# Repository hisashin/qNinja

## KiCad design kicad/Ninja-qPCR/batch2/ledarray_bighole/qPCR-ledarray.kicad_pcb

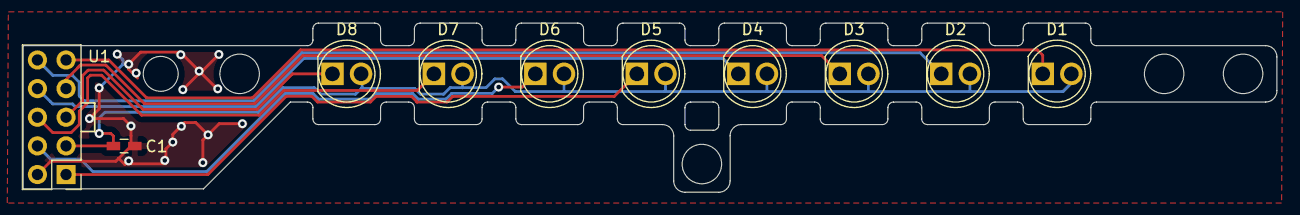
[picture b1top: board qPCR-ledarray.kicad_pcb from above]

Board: 2 copper layers, 111.2 x 15.0 mm, 10 parts (0 on the bottom side), 10 nets.

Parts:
C1: C; C_0603_HandSoldering
D1, D2, D3, D4, D5, D6, D7, D8: LED; LED_D5.0mm
U1: Conn_02x05; Pin_Header_Straight_2x05_Pitch2.54mm

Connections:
GND: C1.2, U1.2
OUT1: D1.1, U1.9
OUT2: D2.1, U1.10
OUT3: D3.1, U1.7
OUT4: D4.1, U1.8
OUT5: D5.1, U1.1
OUT6: D6.1, U1.4
OUT7: D7.1, U1.6
OUT8: D8.1, U1.5
VCC: C1.1, D1.2, D2.2, D3.2, D4.2, D5.2, D6.2, D7.2, D8.2, U1.3

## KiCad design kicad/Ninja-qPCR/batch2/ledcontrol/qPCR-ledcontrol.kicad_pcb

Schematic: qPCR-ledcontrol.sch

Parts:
C1, C2: C; C_0805_HandSoldering
JP1: Jumper_3_Open; SolderJumper-3_P2.0mm_Open_TrianglePad1.0x1.5mm
N_CONN1: Conn_02x05; Con_2x05
S_CONN1: Conn_02x05; Con_2x05
U1: Conn_02x05; Con_2x05
U2: SN74LVC1G04DBVR
U3: MCP4551T-502E_MS; MCP4551T-502E&slash_MS
U4: TLC59281DBQR

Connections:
/LED_IREF: U3.6 (P0W), U4.23 (IREF)
GND: C1.2, C2.2, N_CONN1.2, S_CONN1.2, U1.3, U2.3, U3.4 (VSS), U3.7 (P0B), U4.1 (GND)
I2C_SCL: U1.9, U3.2 (SCL)
I2C_SDA: U1.10, U3.3 (SDA)
LED_BLANK: JP1.2 (C), U4.21 (BLANK)
LED_LAT: U1.5, U4.4 (LAT)
LED_PWM: JP1.1 (A), U1.4, U2.2
LED_SPI_MISO: U1.8, U4.22 (SOUT)
LED_SPI_MOSI: U1.7, U4.2 (SIN)
LED_SPI_SCLK: U1.6, U4.3 (SCLK)
N_LED_OUT1: N_CONN1.9, U4.5 (OUT0)
N_LED_OUT2: N_CONN1.10, U4.6 (OUT1)
N_LED_OUT3: N_CONN1.7, U4.7 (OUT2)
N_LED_OUT4: N_CONN1.8, U4.8 (OUT3)
N_LED_OUT5: N_CONN1.1, U4.9 (OUT4)
N_LED_OUT6: N_CONN1.4, U4.10 (OUT5)
N_LED_OUT7: N_CONN1.6, U4.11 (OUT6)
N_LED_OUT8: N_CONN1.5, U4.12 (OUT7)
unnamed: JP1.3 (B), U2.4
S_LED_OUT1: S_CONN1.9, U4.13 (OUT8)
S_LED_OUT2: S_CONN1.10, U4.14 (OUT9)
S_LED_OUT3: S_CONN1.7, U4.15 (OUT10)
S_LED_OUT4: S_CONN1.8, U4.16 (OUT11)
S_LED_OUT5: S_CONN1.1, U4.17 (OUT12)
S_LED_OUT6: S_CONN1.4, U4.18 (OUT13)
S_LED_OUT7: S_CONN1.6, U4.19 (OUT14)
S_LED_OUT8: S_CONN1.5, U4.20 (OUT15)
VCC_LED: C2.1, N_CONN1.3, S_CONN1.3, U1.1
VCC_LOGIC: C1.1, U1.2, U2.5, U3.1 (HVC/A0), U3.5 (P0A), U3.8 (VDD), U4.24 (VCC)

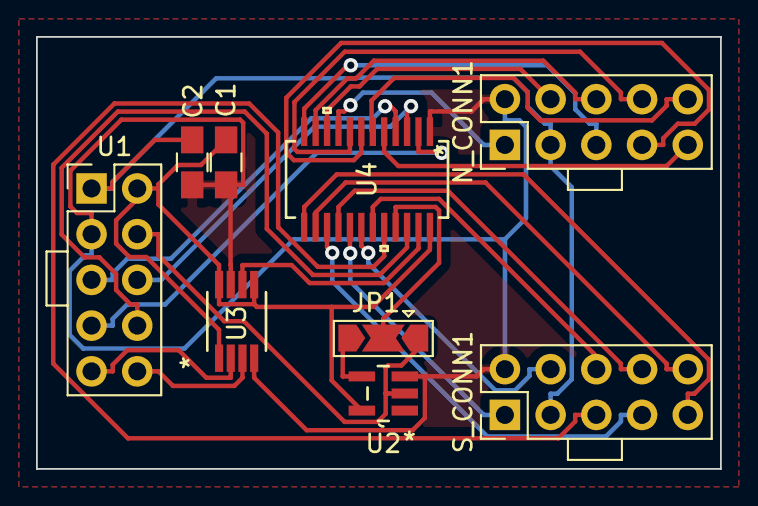
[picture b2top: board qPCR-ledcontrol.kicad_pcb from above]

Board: 2 copper layers, 38.0 x 24.0 mm, 9 parts (0 on the bottom side), 29 nets.

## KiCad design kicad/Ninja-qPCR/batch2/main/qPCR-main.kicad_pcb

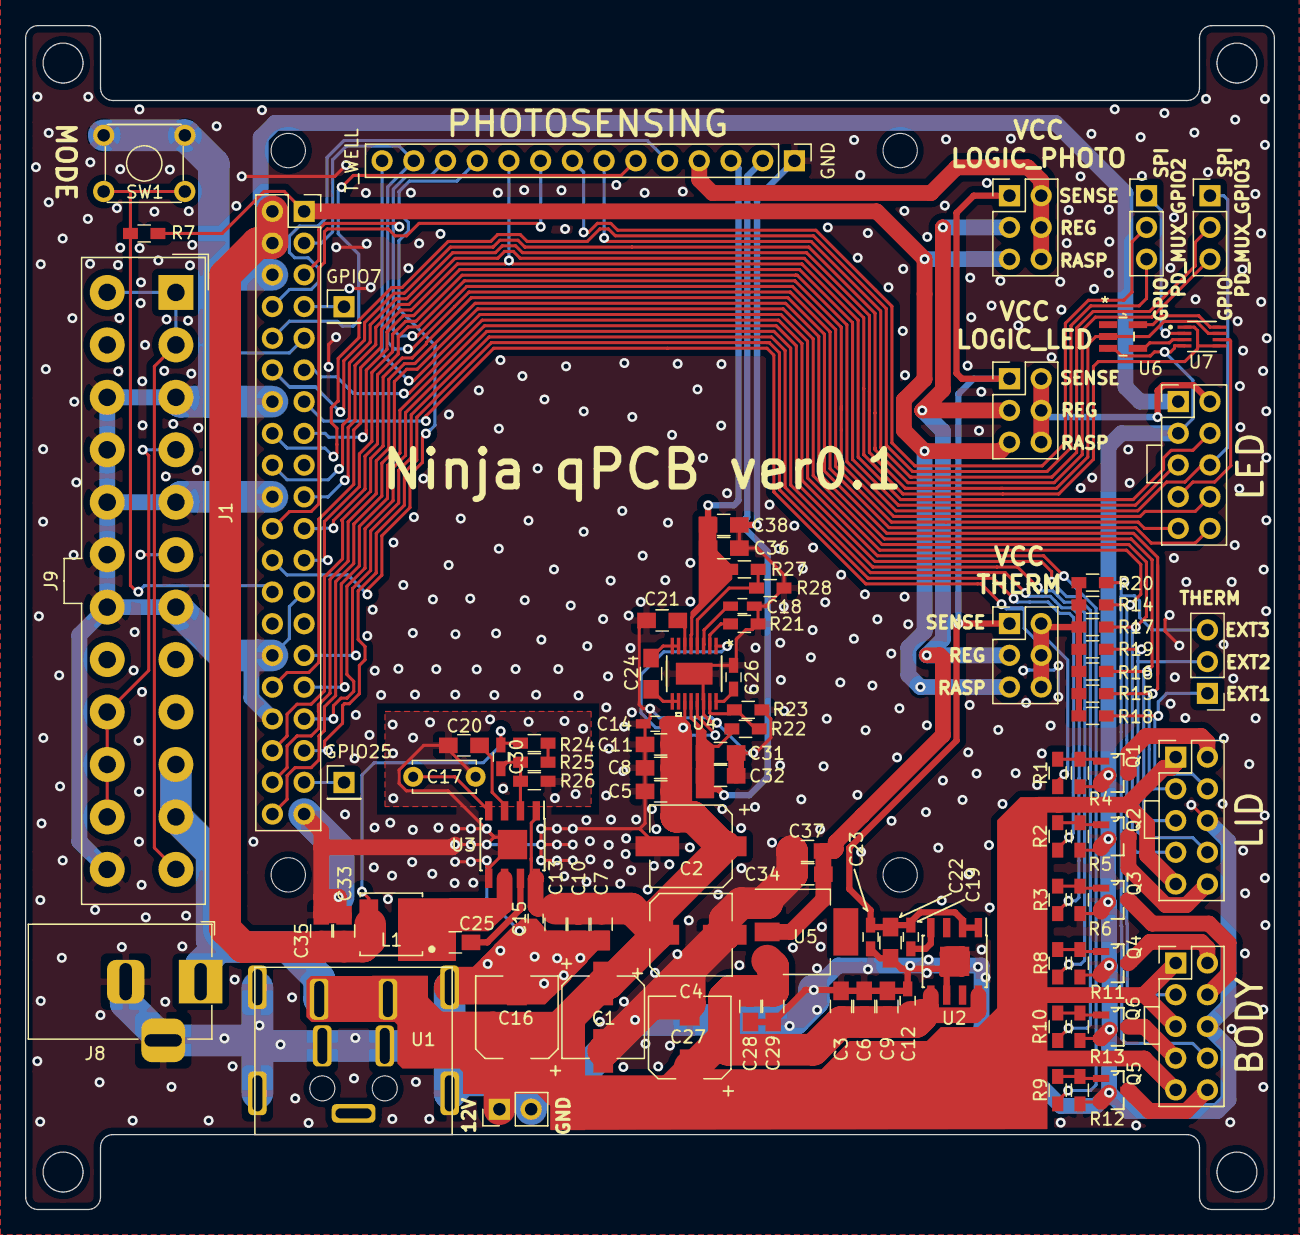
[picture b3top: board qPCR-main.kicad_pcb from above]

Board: 2 copper layers, 100.0 x 94.8 mm, 97 parts (0 on the bottom side), 76 nets.

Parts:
BODY: Conn_02x05; Con_2x05
C1, C2, C4, C16, C27: 100uF; CP_Elec_6.3x5.8
C3, C5, C6, C22, C28, C33, C34, C35: 22uF; C_0805_HandSoldering
C7, C8, C10, C21, C31, C36: 10uF; C_0805_HandSoldering
C9, C11, C13, C25, C29, C32, C37, C38: 0.1uF; C_0805_HandSoldering
C12, C14, C15, C18, C19, C26: 0.01uF; C_0603_HandSoldering
C17: 3300pF; C_Disc_D5.0mm_W2.5mm_P5.00mm
C20, C24: 1uF; C_0805_HandSoldering
C23: 820pF; C_0603_HandSoldering
C30: (5-100pF); C_0603_HandSoldering
GPIO7, GPIO25: Conn_01x01_Male; Pin_Header_Straight_1x01_Pitch2.54mm
J1: Raspberry_Pi_3A_Plus_wpi; Raspberry_Pi_3A+_Socketed_THT_FaceDown_MountingHoles_minimum
J2, J10, J11: Conn_01x03_Male; Pin_Header_Straight_1x03_Pitch2.54mm
J5, J6, J7: Conn_02x03_Odd_Even; Pin_Header_Straight_2x03_Pitch2.54mm
J8: Barrel_Jack_Switch; BarrelJack_Horizontal
J9: ATX-24; Molex_MiniFit-JR-5556-24A_2x12x4.20mm_Straight
J_12V1: Conn_01x02_Male; Pin_Header_Straight_1x02_Pitch2.54mm
L1: 3.3uH(ALPS GLMC / TDK SPM6530); IND_VLS5045EX-4R7M
LED: Conn_02x05; Con_2x05
LID: Conn_02x05; Con_2x05
PHOTOSENSING: Conn_01x14_Male; Pin_Header_Straight_1x14_Pitch2.54mm
Q1, Q2, Q3, Q4, Q5, Q6: Q_NMOS_GSD; SOT95P240X112-3N
R1, R2, R3, R8, R9, R10: 1k; R_0603_HandSoldering
R4, R5, R6, R7, R11, R12, R13: 10k; R_0603_HandSoldering
R14, R15, R16, R17, R18, R19, R20: R; R_0603_HandSoldering
R21: 100K; R_0603_HandSoldering
R22, R27: 22X; R_0603_HandSoldering
R23, R28: 3X; R_0603_HandSoldering
R24: 120k; R_0603_HandSoldering
R25: 1.8k/0; R_0603_HandSoldering
R26: 22k; R_0603_HandSoldering
SW1: TACTILE_4; SW_TH_Tactile_Omron_B3F-10xx
U1: DIN4_PWR; DN4_PWR
U2: IFX1763; SOIC-8-1EP_3.9x4.9mm_Pitch1.27mm
U3: BD9D320EFJ-E2; SOIC-8-1EP_3.9x4.9mm_Pitch1.27mm
U4: LTC3260EMSE-TRPBF
U5: CJT1117-3.3; SOT-223
U6: SN74LVC1G04DBVR
U7: SN74LVC2G66DCUR

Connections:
3V3_REG: C34.1, C37.1, J5.3, J6.3, J7.3, U5.2
3V3_SENSE: C19.1, C22.1, C23.1, J5.1, J6.1, J7.1, U2.1, U2.2
5V: C30.1, C33.1, C35.1, J1.2, J1.4, L1.2, LED.1, R24.1
12V: BODY.1, BODY.5, BODY.9, C1.1, C2.1, C3.1, C4.1, C5.1, C6.1, C7.1, C8.1, C9.1, C10.1, C11.1, C12.1, C13.1, C14.1, C15.1, C16.1, C27.1, C28.1, C29.1, J8.1, J9.10, J9.11, J_12V1.1, LID.1, LID.9, U1.1, U1.2, U2.5, U2.8, U3.1, U3.8, U4.1, U4.11, U4.13, U5.3
+10V: C31.1, C32.1, PHOTOSENSING.2, R22.1, U4.12
-10V: C36.1, C38.1, PHOTOSENSING.3, R27.1, U4.5
/3V3_RASP: J1.1, J5.5, J6.5, J7.5, R7.2
/FAN1: J1.29, R3.2
/FAN2: J1.31, R10.2
/LID_HEATER1: J1.13, R1.2
/LID_HEATER2: J1.35, R2.2
/SheetPower/ADJ+: R22.2, R23.1, U4.15
/SheetPower/ADJ-: R27.2, R28.1, U4.4
/SheetPower/BD_BOOT: C25.1, U3.7
/SheetPower/BD_FB: C30.2, R25.2, R26.1, U3.2
/SheetPower/BD_SW: C25.2, L1.1, U3.6
/SheetPower/C-: C24.2, U4.7, U4.8
/SheetSPI/SPI_SWITCH_INV: U6.4, U7.3
/VCC_LOGIC_LED: J6.2, J6.4, J6.6, LED.2
/VCC_LOGIC_PHOTO: J7.2, J7.4, J7.6, PHOTOSENSING.4
/VCC_THERM: J5.2, J5.4, J5.6, R14.2, R15.2, R16.2, R17.2, R18.2, R19.2, R20.2
/WELL_HEATER1: J1.33, R8.2
/WELL_HEATER2: J1.11, R9.2
ADC_DRDY: J1.24, PHOTOSENSING.11
BODY_HEATER1B: BODY.2, Q4.3
BODY_HEATER2B: BODY.10, Q5.3
FAN_BLACK_GND1: BODY.4, Q3.3
FAN_BLACK_GND2: BODY.7, Q6.3
GND: BODY.6, C1.2, C2.2, C3.2, C4.2, C5.2, C6.2, C7.2, C8.2, C9.2, C10.2, C11.2, C12.2, C13.2, C14.2, C15.2, C16.2, C17.2, C18.2, C20.2, C21.2, C22.2, C23.2, C26.2, C27.2, C28.2, C29.2, C31.2, C32.2, C33.2, C34.2, C35.2, C36.2, C37.2, C38.2, J1.6, J1.9, J1.14, J1.20, J1.25, J1.30, J1.34, J1.39, J8.2, J8.3, J9.3, J9.5, J9.7, J9.15, J9.16, J9.17, J9.18, J9.19, J9.24, J_12V1.2, LED.3, LID.6, PHOTOSENSING.1, Q1.2, Q2.2, Q3.2, Q4.2, Q5.2, Q6.2, R4.1, R5.1, R6.1, R11.1, R12.1, R13.1, R21.2, R23.2, R26.2, R28.2, SW1.3, SW1.4, U1.3, U1.4, U1.6, U1.7, U1.8, U1.9, U2.6, U2.9, U3.5, U3.9, U4.14, U4.EPAD, U5.1, U6.3, U7.4
GPIO7: GPIO7.1, J1.7
GPIO25: GPIO25.1, J1.37
I2C_SCL: J1.5, LED.9, PHOTOSENSING.12
I2C_SDA: J1.3, LED.10, PHOTOSENSING.13
LED_LAT: J1.15, LED.5
LED_SPI_MOSI: LED.7, U7.6
LID_HEATER1B: LID.2, Q1.3
LID_HEATER2B: LID.10, Q2.3
unnamed: C17.1, U3.4
unnamed: C18.1, U4.3
unnamed: C19.2, U2.4
unnamed: C20.1, U3.3
unnamed: C21.1, U4.6
unnamed: C24.1, U4.9, U4.10
unnamed: C26.1, U4.16
unnamed: J1.26, R7.1, SW1.1, SW1.2
unnamed: J9.1, J9.2, J9.12, J9.13
unnamed: J9.4, J9.6, J9.21, J9.22, J9.23
unnamed: Q1.1, R1.1, R4.2
unnamed: Q2.1, R2.1, R5.2
unnamed: Q3.1, R3.1, R6.2
unnamed: Q4.1, R8.1, R11.2
unnamed: Q5.1, R9.1, R12.2
unnamed: Q6.1, R10.1, R13.2
unnamed: R21.1, U4.2
unnamed: R24.2, R25.1
PD_MUX_GPIO1: J1.22, PHOTOSENSING.9
PD_MUX_GPIO2: J10.2, PHOTOSENSING.8
PD_MUX_GPIO2?: J1.16, J10.3
PD_MUX_GPIO3: J11.2, PHOTOSENSING.7
PD_MUX_GPIO3?: J1.12, J11.3
PD_MUX_GPIO4: J1.10, PHOTOSENSING.6
PD_MUX_GPIO5: J1.8, PHOTOSENSING.5
PD_MUX_SPI_MOSI: J10.1, U7.2
PD_REF_PWM: J1.32, LED.4, PHOTOSENSING.10
SPI_MISO: J1.21, LED.8
SPI_MOSI: J1.19, U7.1, U7.5
SPI_SCLK: J1.23, J11.1, LED.6
SPI_SWITCH: J1.18, U6.2, U7.7
THERM_AIR: J1.36, LID.3, R15.1
THERM_EXT1: J2.1, LID.4, R18.1
THERM_EXT2: J2.2, LID.8, R19.1
THERM_EXT3: BODY.8, J2.3, R20.1
THERM_LID1: J1.38, LID.5, R16.1
THERM_LID2: J1.40, LID.7, R17.1
THERM_WELL: BODY.3, PHOTOSENSING.14, R14.1
VCC_LOGIC: U6.5, U7.8

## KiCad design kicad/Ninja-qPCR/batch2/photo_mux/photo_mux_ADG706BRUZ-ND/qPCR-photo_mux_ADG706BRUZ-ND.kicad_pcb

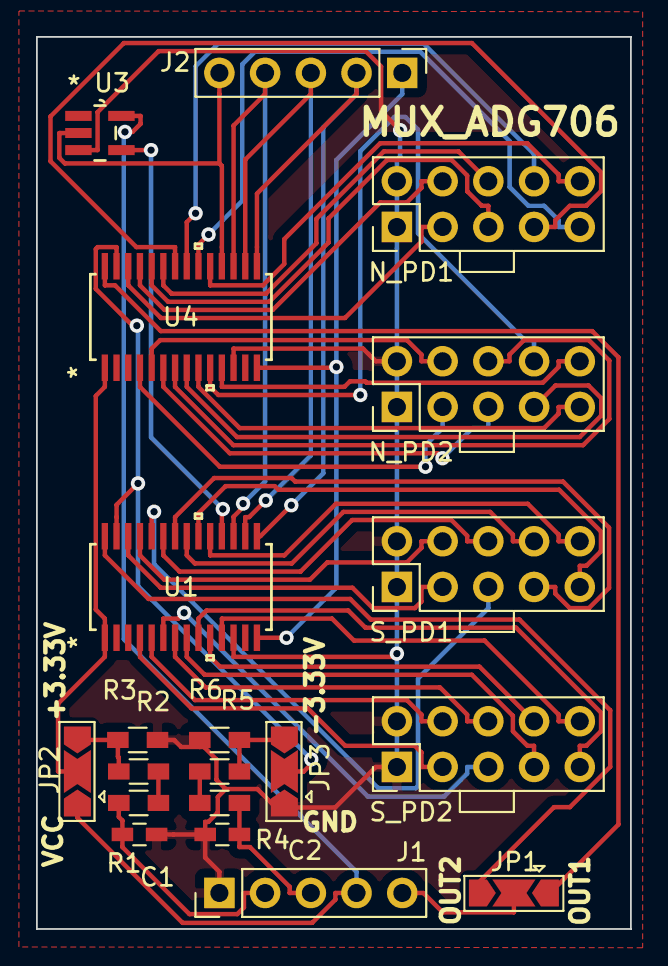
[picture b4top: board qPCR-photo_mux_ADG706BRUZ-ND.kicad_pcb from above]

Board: 2 copper layers, 33.0 x 49.6 mm, 20 parts (0 on the bottom side), 51 nets.

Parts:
C1, C2: C; C_0603_HandSoldering
J1, J2: Conn_01x05_Male; Pin_Header_Straight_1x05_Pitch2.54mm
JP1, JP2, JP3: Jumper_3_Open; SolderJumper-3_P2.0mm_Open_TrianglePad1.0x1.5mm
N_PD1, N_PD2: Conn_02x05; Con_2x05
R1, R2, R3, R4, R5, R6: R; R_0603_HandSoldering
S_PD1, S_PD2: Conn_02x05; Con_2x05
U1, U4: ADG706BRUZ
U3: SN74LVC1G04DBVR

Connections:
+10V: C1.1, J1.2, R1.1
-10V: C2.1, J1.3, R4.1
/+3.33V: JP2.3, R2.2, R3.1
/-3.33V: JP3.3, R5.2, R6.1
/MUX_SELECT_INV: U1.18, U3.4
/PD_MUX_OUT1: JP1.1, U4.28
/PD_MUX_OUT2: JP1.3, U1.28
/VDD: JP2.2, U1.1, U4.1
/VSS: JP3.2, U1.27, U4.27
ADDRESSA0: J2.4, U1.17, U4.17
ADDRESSA1: J2.3, U1.16, U4.16
ADDRESSA2: J2.2, U1.15, U4.15
ADDRESSA3: J2.1, U1.14, U4.14
GND: C1.2, C2.2, J1.1, JP3.1, N_PD1.1, N_PD1.2, N_PD2.1, N_PD2.2, R3.2, R6.2, S_PD1.1, S_PD1.2, S_PD2.1, S_PD2.2, U1.12, U3.3, U4.12
MUX_SELECT: J2.5, U3.2, U4.18
N_PD1_OUT1: N_PD1.10, U4.19
N_PD1_OUT2: N_PD1.9, U4.20
N_PD1_OUT3: N_PD1.8, U4.21
N_PD1_OUT4: N_PD1.7, U4.22
N_PD1_OUT5: N_PD1.6, U4.23
N_PD1_OUT6: N_PD1.5, U4.24
N_PD1_OUT7: N_PD1.4, U4.25
N_PD1_OUT8: N_PD1.3, U4.26
N_PD1_OUT9: N_PD2.10, U4.11
N_PD1_OUT10: N_PD2.8, U4.10
N_PD1_OUT11: N_PD2.9, U4.9
N_PD1_OUT12: N_PD2.7, U4.8
N_PD1_OUT13: N_PD2.6, U4.7
N_PD1_OUT14: N_PD2.5, U4.6
N_PD1_OUT15: N_PD2.4, U4.5
N_PD1_OUT16: N_PD2.3, U4.4
unnamed: R1.2, R2.1
unnamed: R4.2, R5.1
PD_MUX_OUT: J1.5, JP1.2
S_PD1_OUT1: S_PD1.10, U1.19
S_PD1_OUT2: S_PD1.9, U1.20
S_PD1_OUT3: S_PD1.8, U1.21
S_PD1_OUT4: S_PD1.7, U1.22
S_PD1_OUT5: S_PD1.6, U1.23
S_PD1_OUT6: S_PD1.5, U1.24
S_PD1_OUT7: S_PD1.4, U1.25
S_PD1_OUT8: S_PD1.3, U1.26
S_PD1_OUT9: S_PD2.10, U1.11
S_PD1_OUT10: S_PD2.8, U1.10
S_PD1_OUT11: S_PD2.9, U1.9
S_PD1_OUT12: S_PD2.7, U1.8
S_PD1_OUT13: S_PD2.6, U1.7
S_PD1_OUT14: S_PD2.5, U1.6
S_PD1_OUT15: S_PD2.4, U1.5
S_PD1_OUT16: S_PD2.3, U1.4
VCC_LOGIC: J1.4, JP2.1, U3.5

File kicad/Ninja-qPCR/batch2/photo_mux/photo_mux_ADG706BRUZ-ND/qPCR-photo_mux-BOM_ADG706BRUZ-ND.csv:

"Id";"Designator";"Package";"Quantity";"Designation";"Supplier and ref";
1;"C1,C2";"C_0603_HandSoldering";2;"C";;;
2;"J1,J2";"Pin_Header_Straight_1x05_Pitch2.54mm";2;"Conn_01x05_Male";;;
3;"JP1,JP2,JP3";"SolderJumper-3_P2.0mm_Open_TrianglePad1.0x1.5mm";3;"Jumper_3_Open";;;
4;"N_PD1,N_PD2,S_PD1,S_PD2";"Con_2x05";4;"Conn_02x05";;;
5;"R1,R2,R3,R4,R5,R6";"R_0603_HandSoldering";6;"R";;;
6;"U1,U4";"ADG706BRUZ";2;"ADG706BRUZ";;;
7;"U3";"SN74LVC1G04DBVR";1;"SN74LVC1G04DBVR";;;

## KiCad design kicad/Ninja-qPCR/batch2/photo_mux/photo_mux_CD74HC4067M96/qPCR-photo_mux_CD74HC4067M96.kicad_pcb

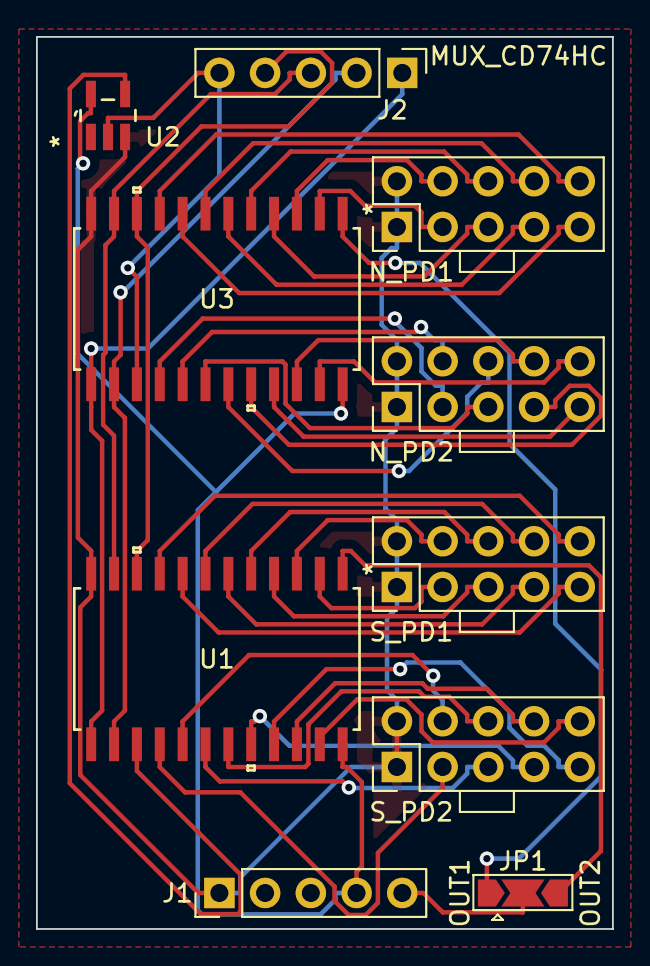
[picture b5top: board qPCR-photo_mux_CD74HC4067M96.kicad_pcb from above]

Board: 2 copper layers, 32.0 x 49.6 mm, 10 parts (0 on the bottom side), 43 nets.

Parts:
J1, J2: Conn_01x05_Male; Pin_Header_Straight_1x05_Pitch2.54mm
JP1: Jumper_3_Open; SolderJumper-3_P2.0mm_Open_TrianglePad1.0x1.5mm
N_PD1, N_PD2: Conn_02x05; Con_2x05
S_PD1, S_PD2: Conn_02x05; Con_2x05
U1, U3: CD74HC4067M96
U2: SN74LVC1G04DBVR

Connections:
/MUX_SELECT_INV: U1.15, U2.4
/PD_MUX_OUT1: JP1.1, U3.1
/PD_MUX_OUT2: JP1.3, U1.1
ADDRESSA0: J2.4, U1.10, U3.10
ADDRESSA1: J2.3, U1.11, U3.11
ADDRESSA2: J2.2, U1.14, U3.14
ADDRESSA3: J2.1, U1.13, U3.13
GND: J1.1, N_PD1.1, N_PD1.2, N_PD2.1, N_PD2.2, S_PD1.1, S_PD1.2, S_PD2.1, S_PD2.2, U1.12, U2.3, U3.12
MUX_SELECT: J2.5, U2.2, U3.15
N_PD1_OUT1: N_PD1.10, U3.9
N_PD1_OUT2: N_PD1.9, U3.8
N_PD1_OUT3: N_PD1.8, U3.7
N_PD1_OUT4: N_PD1.7, U3.6
N_PD1_OUT5: N_PD1.6, U3.5
N_PD1_OUT6: N_PD1.5, U3.4
N_PD1_OUT7: N_PD1.4, U3.3
N_PD1_OUT8: N_PD1.3, U3.2
N_PD1_OUT9: N_PD2.10, U3.23
N_PD1_OUT10: N_PD2.8, U3.22
N_PD1_OUT11: N_PD2.9, U3.21
N_PD1_OUT12: N_PD2.7, U3.20
N_PD1_OUT13: N_PD2.6, U3.19
N_PD1_OUT14: N_PD2.5, U3.18
N_PD1_OUT15: N_PD2.4, U3.17
N_PD1_OUT16: N_PD2.3, U3.16
PD_MUX_OUT: J1.5, JP1.2
S_PD1_OUT1: S_PD1.10, U1.9
S_PD1_OUT2: S_PD1.9, U1.8
S_PD1_OUT3: S_PD1.8, U1.7
S_PD1_OUT4: S_PD1.7, U1.6
S_PD1_OUT5: S_PD1.6, U1.5
S_PD1_OUT6: S_PD1.5, U1.4
S_PD1_OUT7: S_PD1.4, U1.3
S_PD1_OUT8: S_PD1.3, U1.2
S_PD1_OUT9: S_PD2.10, U1.23
S_PD1_OUT10: S_PD2.8, U1.22
S_PD1_OUT11: S_PD2.9, U1.21
S_PD1_OUT12: S_PD2.7, U1.20
S_PD1_OUT13: S_PD2.6, U1.19
S_PD1_OUT14: S_PD2.5, U1.18
S_PD1_OUT15: S_PD2.4, U1.17
S_PD1_OUT16: S_PD2.3, U1.16
VCC_LOGIC: J1.4, U1.24, U2.5, U3.24

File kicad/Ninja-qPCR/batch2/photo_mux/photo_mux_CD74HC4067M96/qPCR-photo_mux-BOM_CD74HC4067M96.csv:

"Id";"Designator";"Package";"Quantity";"Designation";"Supplier and ref";
1;"J1,J2";"Pin_Header_Straight_1x05_Pitch2.54mm";2;"Conn_01x05_Male";;;
2;"JP1";"SolderJumper-3_P2.0mm_Open_TrianglePad1.0x1.5mm";1;"Jumper_3_Open";;;
3;"N_PD1,N_PD2,S_PD1,S_PD2";"Con_2x05";4;"Conn_02x05";;;
4;"U1,U3";"CD74HC4067M96";2;"CD74HC4067M96";;;
5;"U2";"SN74LVC1G04DBVR";1;"SN74LVC1G04DBVR";;;

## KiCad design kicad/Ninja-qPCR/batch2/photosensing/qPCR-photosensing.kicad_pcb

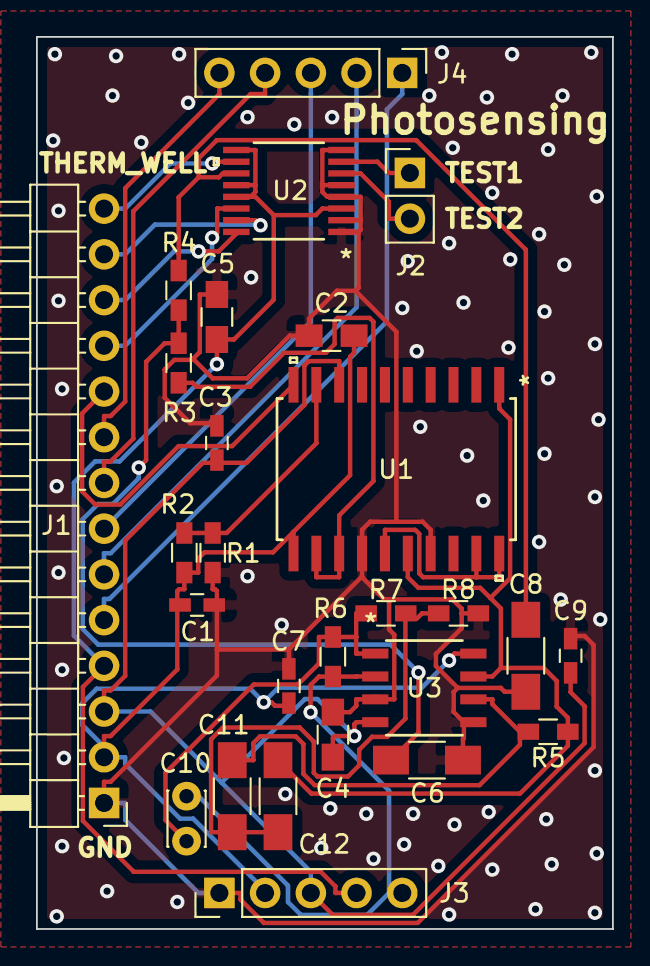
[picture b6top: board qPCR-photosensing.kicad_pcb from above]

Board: 2 copper layers, 32.0 x 49.6 mm, 27 parts (0 on the bottom side), 26 nets.

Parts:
C1, C3, C7, C9: 0.1uF; C_0603_HandSoldering
C2, C4, C5: C; C_0805_HandSoldering
C6, C8: 0.47uF; C_1206_HandSoldering
C10: 10pF; C_Disc_D3.0mm_W2.0mm_P2.50mm
C11, C12: 0.22uF; C_1206_HandSoldering
J1: Conn_01x14_Male; Pin_Header_Angled_1x14_Pitch2.54mm
J2: Conn_01x02_Male; Pin_Header_Straight_1x02_Pitch2.54mm
J3, J4: Conn_01x05_Male; Pin_Header_Straight_1x05_Pitch2.54mm
R1: 1k; R_0603_HandSoldering
R2: 6.2k; R_0603_HandSoldering
R3, R4: 10k; R_0603_HandSoldering
R5: 1800; R_0603_HandSoldering
R6: 1.1M; R_0603_HandSoldering
R7, R8: 560; R_0603_HandSoldering
U1: AD630ARZ
U2: ADS1219IPWR
U3: LME49721MAX_NOPB; LME49721MAX&slash_NOPB

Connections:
+10V: C1.1, C2.1, C7.1, J1.2, J3.2, R2.2, U1.11, U3.8
-10V: C3.1, C4.1, C9.1, J1.3, J3.3, U1.8, U3.4
/AMP_OUT: C12.1, R5.1, U1.1, U1.16, U3.7
/PHOTO_OUT: C8.2, R4.2, U2.11
ADC_DRDY: J1.11, U2.14
GND: C1.2, C2.2, C3.2, C4.2, C5.2, C6.2, C7.2, C8.1, C9.2, J1.1, J3.1, R1.1, R8.2, U1.14, U1.17, U2.1, U2.2, U2.4, U2.5, U2.8, U3.3, U3.5
I2C_SCL: J1.12, U2.16
I2C_SDA: J1.13, U2.15
unnamed: C6.1, R3.1, R4.1
unnamed: C10.2, R6.2, R7.2, U3.1
unnamed: C11.1, R5.2, U3.6
unnamed: C11.2, C12.2, R7.1, R8.1
unnamed: R1.2, R2.1, U1.9
unnamed: R3.2, U1.12, U1.13
unnamed: U1.15, U1.19, U1.20
PD_MUX_GPIO1: J1.9, J4.5
PD_MUX_GPIO2: J1.8, J4.4
PD_MUX_GPIO3: J1.7, J4.3
PD_MUX_GPIO4: J1.6, J4.2
PD_MUX_GPIO5: J1.5, J4.1
PD_MUX_OUT: C10.1, J3.5, R6.1, U3.2
PD_REF_PWM: J1.10, U1.10
THERM_TEST1: J2.1, U2.7
THERM_TEST2: J2.2, U2.6
THERM_WELL: J1.14, U2.10
VCC_LOGIC: C5.1, J1.4, J3.4, U2.3, U2.9, U2.12, U2.13

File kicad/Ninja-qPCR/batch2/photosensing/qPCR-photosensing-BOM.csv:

"Id";"Designator";"Package";"Quantity";"Designation";"Supplier and ref";
1;"C1,C3,C7,C9";"R_0603_HandSoldering";4;"0.1uF";;;
2;"C8,C6";"R_1206_HandSoldering";2;"0.47uF";;;
3;"J3,J4";"Pin_Header_Straight_1x05_Pitch2.54mm";2;"Conn_01x05_Male";;;
4;"R1";"R_0603_HandSoldering";1;"1k";;;
5;"R2";"R_0603_HandSoldering";1;"6.2k";;;
6;"R3,R4";"R_0603_HandSoldering";2;"10k";;;
7;"R5";"R_0603_HandSoldering";1;"1800";;;
8;"R6";"R_0603_HandSoldering";1;"1.1M";;;
9;"R7,R8";"R_0603_HandSoldering";2;"560";;;
10;"U1";"AD630ARZ";1;"AD630ARZ";;;
11;"U2";"ADS1219IPWR";1;"ADS1219IPWR";;;
12;"U3";"LME49721MAX&slash_NOPB";1;"LME49721MAX_NOPB";;;
13;"C2,C4,C5";"C_0805_HandSoldering";3;"C";;;
14;"C10";"C_Disc_D3.0mm_W2.0mm_P2.50mm";1;"10pF";;;
15;"C11,C12";"R_1206_HandSoldering";2;"0.22uF";;;
16;"J1";"Pin_Header_Angled_1x14_Pitch2.54mm";1;"Conn_01x14_Male";;;
17;"J2";"Pin_Header_Straight_1x02_Pitch2.54mm";1;"Conn_01x02_Male";;;

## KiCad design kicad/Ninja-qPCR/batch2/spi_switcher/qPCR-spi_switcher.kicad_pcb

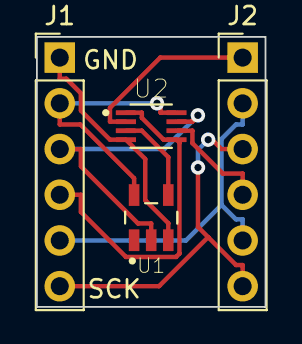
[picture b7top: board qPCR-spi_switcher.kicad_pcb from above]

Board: 2 copper layers, 12.7 x 15.0 mm, 4 parts (0 on the bottom side), 9 nets.

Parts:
J1, J2: Conn_01x06_Male; Pin_Header_Straight_1x06_Pitch2.54mm
U1: SN74LVC1G04DBVR; SN74LVC1G66DBVR
U2: SN74LVC2G66DCUR

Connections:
/INV: U1.4, U2.3
GND: J1.1, U1.3, U2.4
MISO: J1.5, J2.2, J2.5
MOSI: J1.4, U2.1, U2.5
MOSI1: J2.1, U2.2
MOSI2: J2.4, U2.6
SCK: J1.6, J2.3, J2.6
SPI_MOSI_SWITCH: J1.3, U1.2, U2.7
VCC: J1.2, U1.5, U2.8

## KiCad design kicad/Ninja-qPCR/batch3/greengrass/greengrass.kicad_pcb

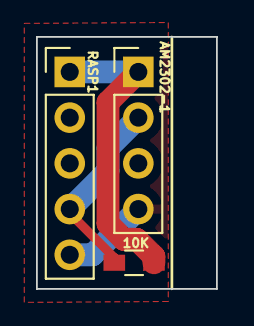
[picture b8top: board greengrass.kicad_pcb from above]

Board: 2 copper layers, 10.0 x 14.0 mm, 3 parts (0 on the bottom side), 3 nets.

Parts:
J1: Conn_01x05_Male; Pin_Header_Straight_1x05_Pitch2.54mm
J3: Conn_01x04_Male; Pin_Header_Straight_1x04_Pitch2.54mm
R1: 10K; R_0603_HandSoldering

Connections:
+3V3: J1.1, J3.1, R1.1
/SCA: J1.4, J3.2, R1.2
GND: J1.5, J3.4

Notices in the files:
parts and their libraries:
Copyright 2016 Accelerated Designs. All rights reserved.
